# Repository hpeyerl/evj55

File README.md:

# Before

# Maybe

Files related to my EV conversion project.

## Related repos

- [evj55-dashboard](https://github.com/hpeyerl/evj55-dashboard) - dashboard firmware (Radxa CM3 + dual-CAN HAT+)
- [Wiring Harness](wiring/splice-cad-rendered/EVJ-55_plan_all_pages_schematic.pdf)

# Network system diagram

# Mechanical/Electrical system diagram

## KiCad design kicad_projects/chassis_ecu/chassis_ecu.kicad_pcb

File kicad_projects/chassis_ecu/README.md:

# chassis_ecu

ESP32-S3 CAN board for the parking pawl, J1772 pilot and contactor-weld sense.
The EPB stays on the Revus controller. Spec: `evj55_contexts/CHASSIS_ECU_CONTEXT.md`.

The schematic is generated. Edit `gen/chassis_ecu.py`, then:

    cd gen && /usr/bin/python3 build.py

`build.py` rewrites the `*.kicad_sch` files, runs `kicad-cli` ERC, and checks the exported
netlist against the definition (every pin on its intended net). Use the system python: KiCad's
libraries and `pcbnew` are installed there.

Parts are hand-placed in the generator and wired; the generator is the master copy (do not save
schematic edits made in KiCad).

## Requirements
What the schematic must satisfy. Review against these.

**Jobs:** parking-pawl drive, J1772 car-side pilot (CP) and proximity (PP), contactor-weld sense,
brake / P-position inputs, 2 analog inputs, 6-axis IMU, one CAN bus. The EPB is NOT on this board.

**Supply (J20 A2, switched 12V):**
- Steady state <= 15 V (DC-DC fed, no alternator). Spikes from inductive kickback, wiring ring and
  terminal let-go (microseconds) must be clamped; no sustained overvoltage.
- Reverse battery must not damage the logic side and must not blow the board fuse.
- Starts at about 6 V (UVLO). 3.3 V rail >= 1 A (ESP32 + CAN + sensors, ~0.6 A peak estimate).
- Low sleep current is wanted (an optional harness change feeds the board from permanent B+).

**Opto inputs x4 (J20 B2-B5: P_SENSE, BRAKE, WELD1, WELD2):** 12V-active, opto-coupled (level shift
and robustness; NOT isolated - the inputs share vehicle GND), active-low at the GPIO, filtered.
WELD1/WELD2 are the contactors' dry aux contacts (open = no voltage). P_SENSE taps a sense line shared with other loads, so it must draw little current.

**Pawl output (J20 A1/B1 feed, A8/B8 out):** high-side 12 V switch to the actuator (the actuator's
other lead grounds at the motor). Current sense for stall detection; firmware enforces a run
timeout. Design stall current 20 A (actual stall current not yet measured). No reverse protection on
the motor feed: the external harness fuse protects it.

**J1772 (J20 C2 CP, C3 CP_GND, C4 PP), car side - the board never generates the pilot:**
- CP -> diode -> 2.74 k to GND (state B); + 1.3 k switched in parallel (state C).
- The state-C switch must be CLOSED when the board is unpowered (12V box dead before AC arrives,
  so a dead board must still request charge). Firmware opens it to hold state B (pause / stop).
- Read CP duty (1 kHz, 10-96 %) and CP high level (+12 / +9 / +6 V = state A / B / C).
- Survive the +/-12 V CP swing; load on CP >= 100 k.
- Read PP: open / plug inserted / latch button pressed must be distinguishable.

**CAN:** one classic CAN bus (truck CAN1), in and out pins on J20 for daisy-chaining. No glitch
on CAN TX at power-up. Transceiver standby under firmware control (sleep current). 120R
terminator selectable, default off (mid-bus). Bus TVS. Firmware emulates the Zombie CPC (TX 0x357,
RX 0x358).

**Analog inputs AIN1/AIN2 (J20 B6/B7):** 0-15 V into the ESP32 ADC1 (effective range 0-2.9 V), survive reverse / overvoltage
spikes. Coarse accuracy is fine. 12 V logic supply sensed on ADC1 as well.

**IMU:** 6-axis accel + gyro on I2C, no magnetometer. The board mounts square to the vehicle axes.

**MCU / debug:** ESP32-S3 module with PCB antenna (plastic case). USB for programming (data only;
the board runs from 12 V). UART header (DNP) as a fallback console. BOOT / RESET as jumper pads.
Expansion header J10 (DNP): I2C, 3 raw ADC1, 2 GPIO.

**Mechanical / manufacture:**
- PCB 82 x 101 mm in the case; J20 centred on an 82 mm edge.
- Case height 33 mm only over the third nearest J20: tall parts go there.
- JLC assembly with LCSC parts; J20 and test points are hand-soldered.
- A labelled GND test point for scope / logic-analyser clips.
- Automotive: conformal coat.

## PCB
`chassis_ecu.kicad_pcb` was created once by `gen/make_pcb.py`: 82 x 101 mm outline (3 mm corners,
J20 key notch), 4 layers, J20 centred on the top edge, ESP32 antenna flush with the bottom edge
(copper keep-out under it), case holes, first-pass block placement (tall parts in the top third).
The script refuses to overwrite an existing board (`--force` discards it). From here: edit in KiCad,
"Update PCB from Schematic" after schematic changes. Expected DRC items: U2 courtyard (on-board
antenna keep-out, not used here) and the paired case holes H1/H2, H3/H4 overlap.

## Parts / BOM
- `gen/jlc_select.py <cache.sqlite3>` picks LCSC parts from the jlcparts database
  (yaqwsx.github.io/jlcparts/data/cache.zip + cache.z01..z05, a split zip of one 2.1 GB sqlite file;
  the concatenated parts start with a 4-byte split marker) and writes `gen/lcsc_parts.json`.
  Preference: in stock, JLC basic > preferred > extended.
- `gen/bom.py` writes `chassis_ecu_bom_jlc.csv` (JLCPCB assembly format).
- U2 = ESP32-S3-WROOM-1-N4 (LCSC C2913197), JLC-assembled; 4 MB = 2 x ~1.9 MB OTA slots (min_spiffs).
  Not assembled by JLC: connectors (J20 = through-hole), BOOT/RESET jumper pads,
  solder jumpers, test points.
- 55 BOM lines, 117 placements. Low JLC stock (< 5000) on the
  BTN8982TA, CPC1117N, FDD4685, LSM6DSOX, SMCJ22A, TLV3201 - recheck at order time.

## Status
- Drawn (0 ERC errors, netlist self-check OK): Power, MCU, CAN (1 bus, native TWAI), IO (4 opto
  inputs, status LEDs, J10 expansion), Motors (pawl high-side, BTN8982TA), J1772 (CP state + read,
  PP read), Sensors (LSM6DSO, 2x 12V-tolerant AIN), Connector.
- Main connector J20 = Aptiv/FCI HCCPHPE24BKA90F (24-way 90 deg, key A), mates 211PC249S0005.
  Footprint from FCI drawing FSC 308654: `lib/` (generated by `gen/make_lib.py`). Footprint
  confirmed with a 1:1 printout against a real header.
- Case (listing drawing, to verify on the real part): PCB 82 x 101 mm; J20 centred on an 82 mm edge;
  4x 2.5 mm mounting holes = 2 slotted pairs (6 mm apart) at 62.2 mm centres, lower holes 7.4 mm from
  the edge opposite J20. Case outside 120 x 121 x 33 mm.
- 3D model: vendor STEP is not redistributable; put `HCCPHPE24BKA90F.stp` in `lib/3d/` (git-ignored).
- 4 ERC warnings: the SparkFun LSM6DSOX symbol types its strap pins bidirectional (benign).
- Design stall current 20 A.  PP is read on this board
  (Zombie `interface=CPC`).  Open: routing.

## ESP32-S3 pin map
| GPIO | Net | GPIO | Net |
|---|---|---|---|
| IO0 | ESP_BOOT (JP4 pad) | IO35-38 | OPTO_IN1-4 (P_SENSE, BRAKE, WELD1, WELD2; active-low) |
| IO1 | CP_LVL (ADC1) | IO39 | PAWL_INH (10k pull-down) |
| IO2 | PP_SENSE (ADC1) | IO40 | CAN1_TXD |
| IO4 / IO5 / IO10 | ANA1-3 (ADC1, J10) | IO21 | CAN1_RXD |
| IO6 | PAWL_IS (ADC1) | IO41 | CP_DUTY |
| IO7 | VSENSE_12V (ADC1) | IO42 | CP_S2_OPEN |
| IO8 / IO9 | AIN1 / AIN2 (ADC1, J20) | IO47 | IMU_INT1 |
| IO11 / IO12 | EXP_GPIO1 / 2 (J10) | IO48 | PAWL_DRV |
| IO15 / IO16 | I2C_SDA / I2C_SCL | IO17 / IO18 | LED_STAT1 / LED_STAT2 |
| IO13 | CAN1_RS (low = run, high = standby; 10k pull-down) | | |
| IO19 / IO20 | USB D- / D+ | IO43 / IO44 | UART TX / RX (J2, DNP) |
| unused | IO14 | strapping, NC | IO3, IO45, IO46 |

## I2C
0x6A LSM6DSO. J10 brings the bus out for add-ons.

## J10 expansion (DNP)
1 GND, 2 3V3, 3 SDA, 4 SCL, 5-7 ANA1-3 (raw ADC1, 0-2.9 V), 8-9 EXP_GPIO1/2, 10 GND.

## J20 pinout (columns 1 and 8 = high-current cavities)
| Pin | Net | Pin | Net | Pin | Net |
|---|---|---|---|---|---|
| A1 | PAWL_12V | B1 | PAWL_12V | C1 | GND |
| A2 | VIN_12V | B2 | IN_P_SENSE | C2 | CP |
| A3 | CAN1_H in | B3 | IN_BRAKE | C3 | CP_GND |
| A4 | CAN1_L in | B4 | IN_WELD1 | C4 | PP |
| A5 | CAN1_H out | B5 | IN_WELD2 | C5 | spare |
| A6 | CAN1_L out | B6 | AIN1 (0-15 V) | C6 | spare |
| A7 | GND | B7 | AIN2 (0-15 V) | C7 | spare |
| A8 | MOT_OUT | B8 | MOT_OUT | C8 | GND |

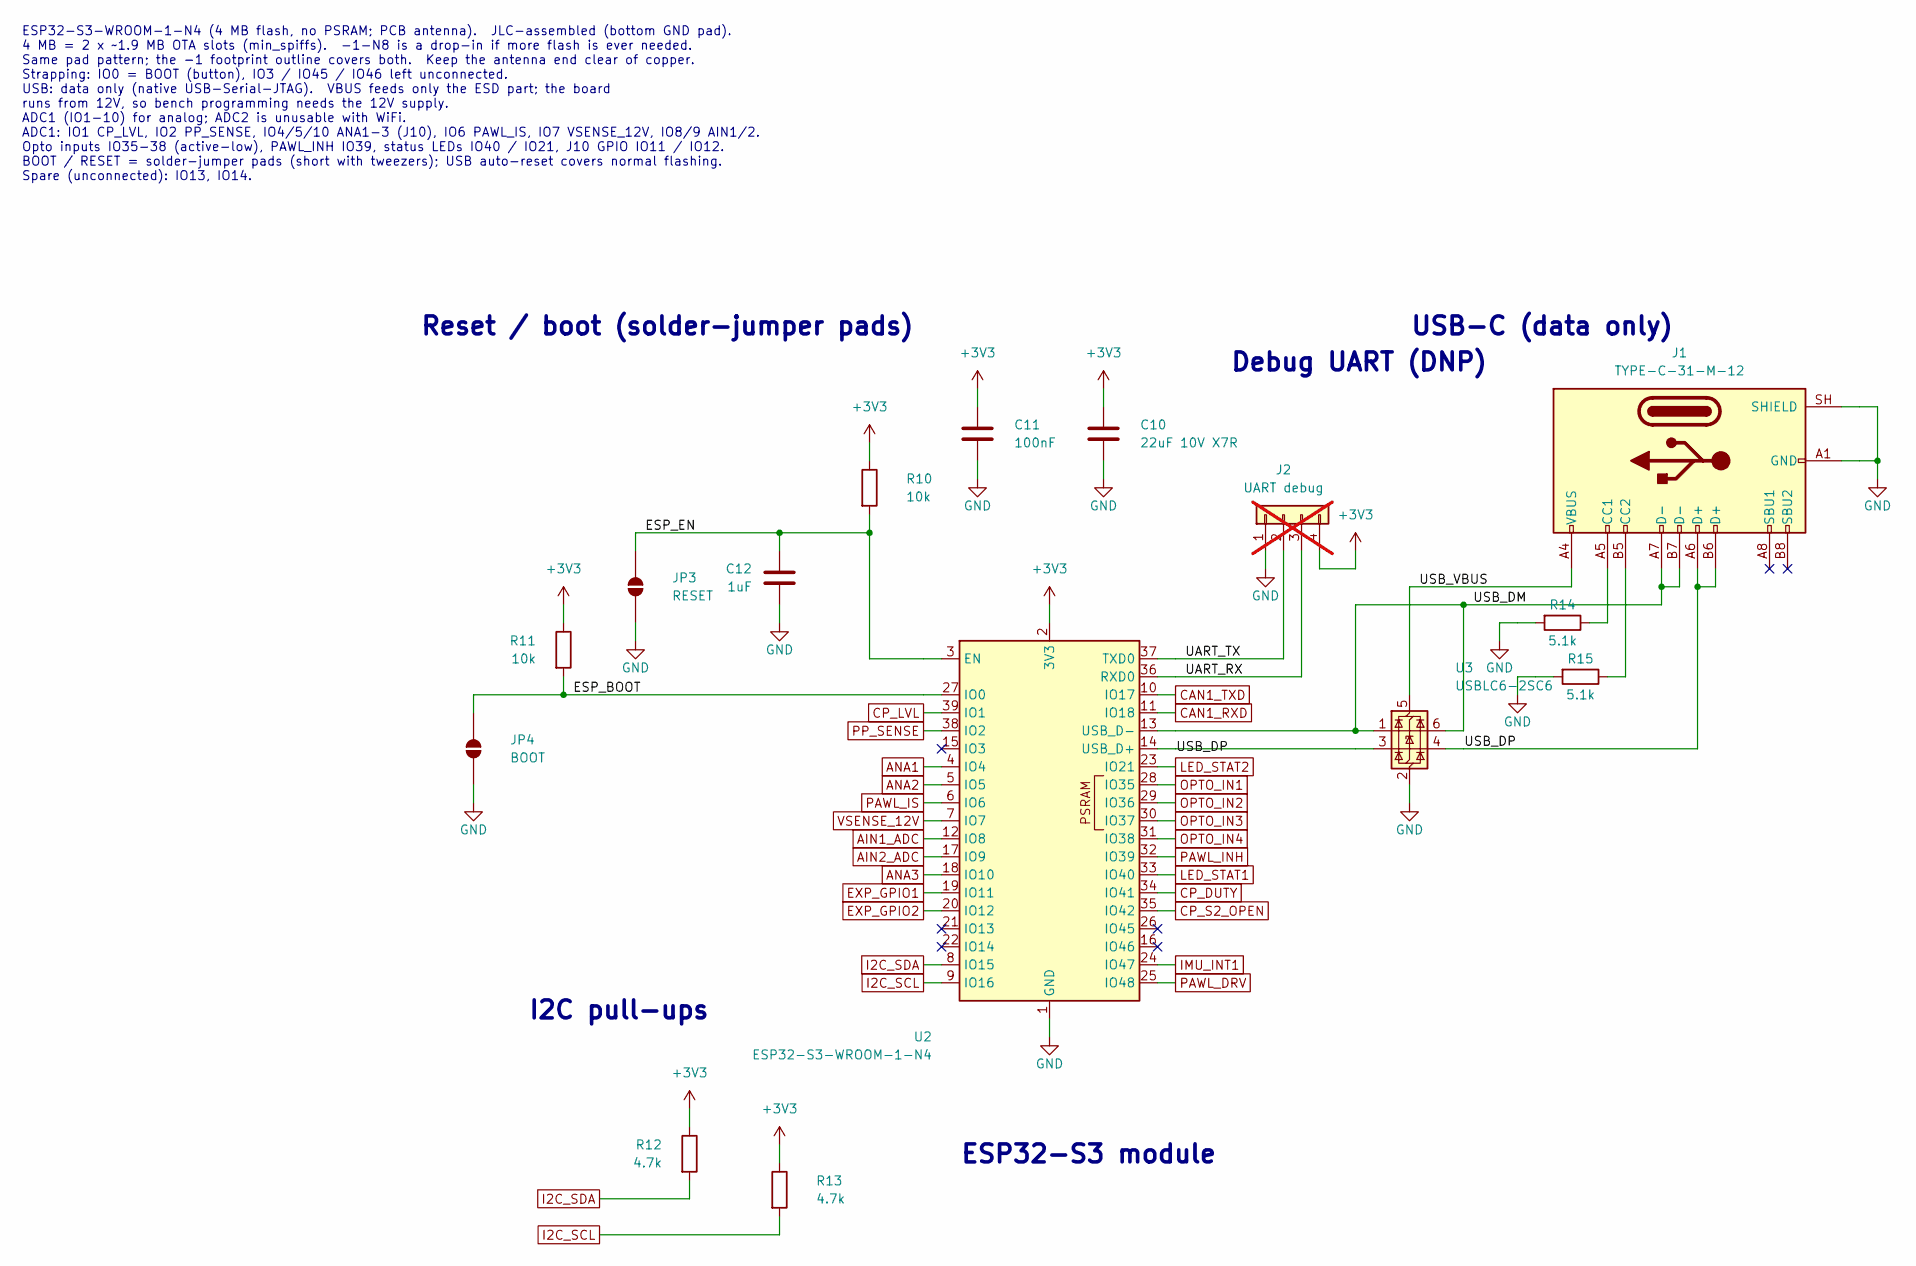
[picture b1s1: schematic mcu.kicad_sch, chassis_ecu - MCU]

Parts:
C10: 22uF 10V X7R; C_1206_3216Metric; MPN CL31A226KAHNNNE; LCSC C12891
C11: 100nF; C_0603_1608Metric; MPN CC0603KRX7R9BB104; LCSC C14663
C12: 1uF; C_0603_1608Metric; MPN CL10A105KB8NNNC; LCSC C15849
J1: TYPE-C-31-M-12; USB_C_Receptacle_HRO_TYPE-C-31-M-12; MPN TYPE-C-31-M-12; LCSC C165948
J2: UART debug; PinHeader_1x04_P2.54mm_Vertical; not fitted
JP3: RESET; SolderJumper-2_P1.3mm_Open_RoundedPad1.0x1.5mm; MPN TS-1187A-B-A-B; LCSC C318884
JP4: BOOT; SolderJumper-2_P1.3mm_Open_RoundedPad1.0x1.5mm; MPN TS-1187A-B-A-B; LCSC C318884
R10, R11: 10k; R_0603_1608Metric; MPN 0603WAF1002T5E; LCSC C25804
R12, R13: 4.7k; R_0603_1608Metric; MPN 0603WAF4701T5E; LCSC C23162
R14, R15: 5.1k; R_0603_1608Metric; MPN 0603WAF5101T5E; LCSC C23186
U2: ESP32-S3-WROOM-1-N4; ESP32-S3-WROOM-1; LCSC C2913197
U3: USBLC6-2SC6; SOT-23-6; MPN USBLC6-2SC6; LCSC C7519

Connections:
+3V3: C10.1, C11.1, J2.4, R10.1, R11.1, R12.1, R13.1, U2.2 (3V3); also elsewhere on the board
/MCU/ESP_BOOT: JP4.1 (A), R11.2, U2.27 (IO0)
/MCU/ESP_EN: C12.1, JP3.1 (A), R10.2, U2.3 (EN)
/MCU/UART_RX: J2.3, U2.36 (RXD0)
/MCU/UART_TX: J2.2, U2.37 (TXD0)
/MCU/USB_CC1: J1.A5 (CC1), R14.1
/MCU/USB_CC2: J1.B5 (CC2), R15.1
/MCU/USB_DM: J1.A7 (D-), J1.B7 (D-), U2.13 (USB_D-), U3.1 (I/O1), U3.6 (I/O1)
/MCU/USB_DP: J1.A6 (D+), J1.B6 (D+), U2.14 (USB_D+), U3.3 (I/O2), U3.4 (I/O2)
/MCU/USB_VBUS: J1.A4 (VBUS), J1.A9 (VBUS), J1.B4 (VBUS), J1.B9 (VBUS), U3.5 (VBUS)
AIN1_ADC: U2.12 (IO8); also elsewhere on the board
AIN2_ADC: U2.17 (IO9); also elsewhere on the board
ANA1: U2.4 (IO4); also elsewhere on the board
ANA2: U2.5 (IO5); also elsewhere on the board
ANA3: U2.18 (IO10); also elsewhere on the board
CAN1_RXD: U2.11 (IO18); also elsewhere on the board
CAN1_TXD: U2.10 (IO17); also elsewhere on the board
CP_DUTY: U2.34 (IO41); also elsewhere on the board
CP_LVL: U2.39 (IO1); also elsewhere on the board
CP_S2_OPEN: U2.35 (IO42); also elsewhere on the board
EXP_GPIO1: U2.19 (IO11); also elsewhere on the board
EXP_GPIO2: U2.20 (IO12); also elsewhere on the board
GND: C10.2, C11.2, C12.2, J1.A1 (GND), J1.A12 (GND), J1.B1 (GND), J1.B12 (GND), J1.SH (SHIELD), J2.1, JP3.2 (B), JP4.2 (B), R14.2, R15.2, U2.1 (GND), U2.40 (GND), U2.41 (GND), U3.2 (GND); also elsewhere on the board
I2C_SCL: R13.2, U2.9 (IO16); also elsewhere on the board
I2C_SDA: R12.2, U2.8 (IO15); also elsewhere on the board
IMU_INT1: U2.24 (IO47); also elsewhere on the board
LED_STAT1: U2.33 (IO40); also elsewhere on the board
LED_STAT2: U2.23 (IO21); also elsewhere on the board
OPTO_IN1: U2.28 (IO35); also elsewhere on the board
OPTO_IN2: U2.29 (IO36); also elsewhere on the board
OPTO_IN3: U2.30 (IO37); also elsewhere on the board
OPTO_IN4: U2.31 (IO38); also elsewhere on the board
PAWL_DRV: U2.25 (IO48); also elsewhere on the board
PAWL_INH: U2.32 (IO39); also elsewhere on the board
PAWL_IS: U2.6 (IO6); also elsewhere on the board
PP_SENSE: U2.38 (IO2); also elsewhere on the board
VSENSE_12V: U2.7 (IO7); also elsewhere on the board

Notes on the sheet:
I2C pull-ups
Debug UART (DNP)
ESP32-S3-WROOM-1-N4 (4 MB flash, no PSRAM; PCB antenna). JLC-assembled (bottom GND pad). 4 MB = 2 x ~1.9 MB OTA slots (min_spiffs). -1-N8 is a drop-in if more flash is ever needed. Same pad pattern; the -1 footprint outline covers both. Keep the antenna end clear of copper. Strapping: IO0 = BOOT (b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
Reset / boot (solder-jumper pads)
ESP32-S3 module
USB-C (data only)

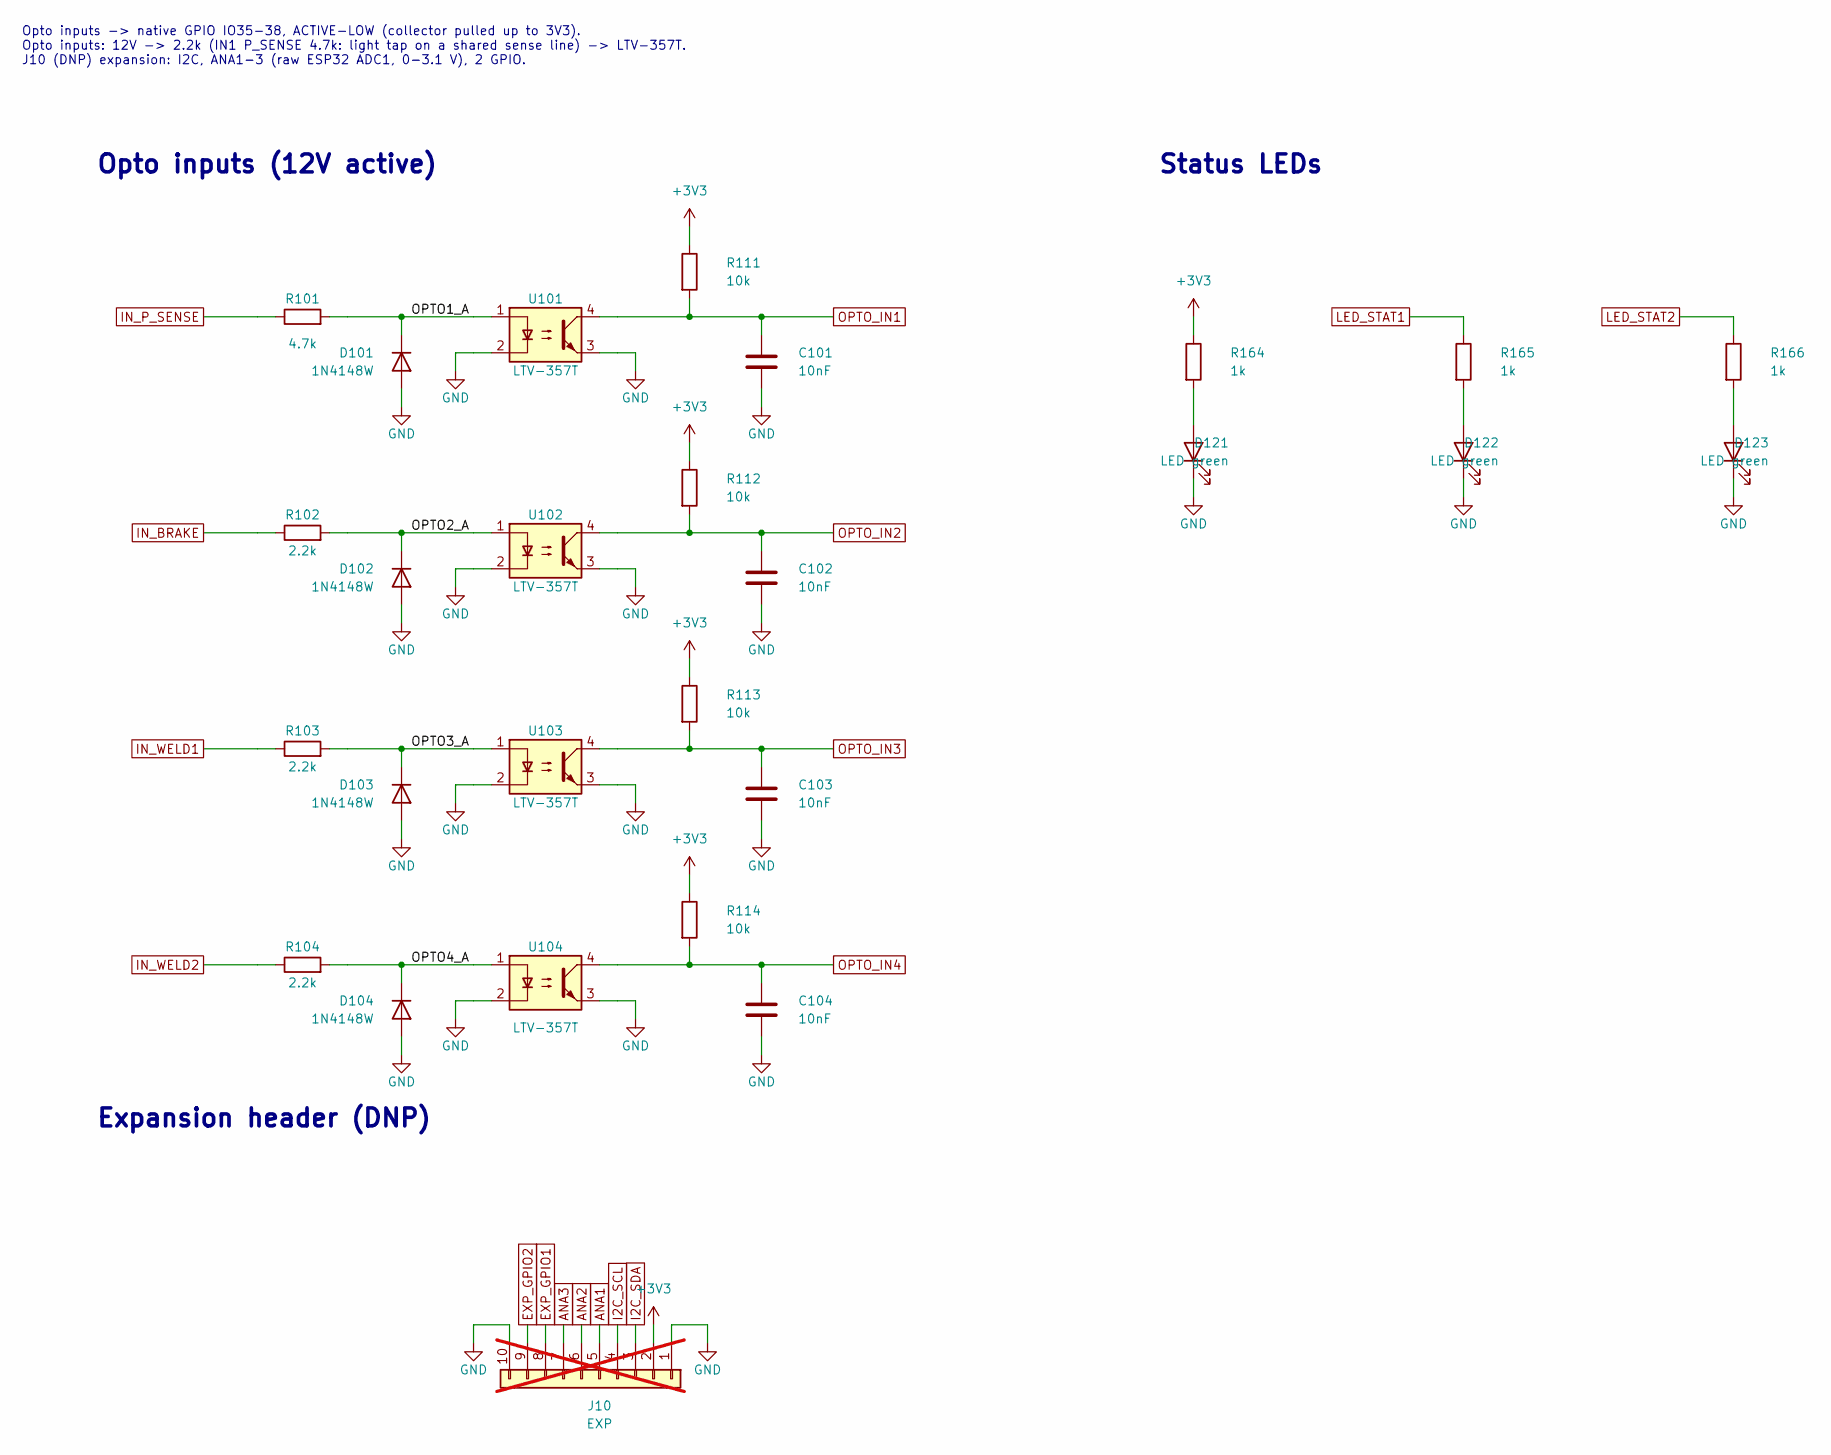
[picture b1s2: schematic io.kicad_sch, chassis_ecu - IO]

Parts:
C101, C102, C103, C104: 10nF; C_0603_1608Metric; MPN 0603B103K500NT; LCSC C57112
D101, D102, D103, D104: 1N4148W; D_SOD-123; MPN 1N4148W; LCSC C81598
D121, D122, D123: LED green; LED_0603_1608Metric; MPN F.0603.00025/P2-0603G1TS2-06T-002; LCSC C7496818
J10: EXP; PinHeader_1x10_P2.54mm_Vertical; not fitted
R101: 4.7k; R_0805_2012Metric; MPN 0805W8F4701T5E; LCSC C17673
R102, R103, R104: 2.2k; R_0805_2012Metric; MPN 0805W8F2201T5E; LCSC C17520
R111, R112, R113, R114: 10k; R_0603_1608Metric; MPN 0603WAF1002T5E; LCSC C25804
R164, R165, R166: 1k; R_0603_1608Metric; MPN 0603WAF1001T5E; LCSC C21190
U101, U102, U103, U104: LTV-357T; SO-4_4.4x3.6mm_P2.54mm; MPN LTV-357T-C; LCSC C119091

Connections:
+3V3: J10.2, R111.1, R112.1, R113.1, R114.1, R164.1; also elsewhere on the board
/IO/LED1_A: D122.2 (A), R165.2
/IO/LED2_A: D123.2 (A), R166.2
/IO/LED_PWR_A: D121.2 (A), R164.2
/IO/OPTO1_A: D101.1 (K), R101.2, U101.1
/IO/OPTO2_A: D102.1 (K), R102.2, U102.1
/IO/OPTO3_A: D103.1 (K), R103.2, U103.1
/IO/OPTO4_A: D104.1 (K), R104.2, U104.1
ANA1: J10.5; also elsewhere on the board
ANA2: J10.6; also elsewhere on the board
ANA3: J10.7; also elsewhere on the board
EXP_GPIO1: J10.8; also elsewhere on the board
EXP_GPIO2: J10.9; also elsewhere on the board
GND: C101.2, C102.2, C103.2, C104.2, D101.2 (A), D102.2 (A), D103.2 (A), D104.2 (A), D121.1 (K), D122.1 (K), D123.1 (K), J10.1, J10.10, U101.2, U101.3, U102.2, U102.3, U103.2, U103.3, U104.2, U104.3; also elsewhere on the board
I2C_SCL: J10.4; also elsewhere on the board
I2C_SDA: J10.3; also elsewhere on the board
IN_BRAKE: R102.1; also elsewhere on the board
IN_P_SENSE: R101.1; also elsewhere on the board
IN_WELD1: R103.1; also elsewhere on the board
IN_WELD2: R104.1; also elsewhere on the board
LED_STAT1: R165.1; also elsewhere on the board
LED_STAT2: R166.1; also elsewhere on the board
OPTO_IN1: C101.1, R111.2, U101.4; also elsewhere on the board
OPTO_IN2: C102.1, R112.2, U102.4; also elsewhere on the board
OPTO_IN3: C103.1, R113.2, U103.4; also elsewhere on the board
OPTO_IN4: C104.1, R114.2, U104.4; also elsewhere on the board

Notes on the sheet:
Opto inputs (12V active)
Opto inputs -> native GPIO IO35-38, ACTIVE-LOW (collector pulled up to 3V3). Opto inputs: 12V -> 2.2k (IN1 P_SENSE 4.7k: light tap on a shared sense line) -> LTV-357T. J10 (DNP) expansion: I2C, ANA1-3 (raw ESP32 ADC1, 0-3.1 V), 2 GPIO.
Status LEDs
Expansion header (DNP)

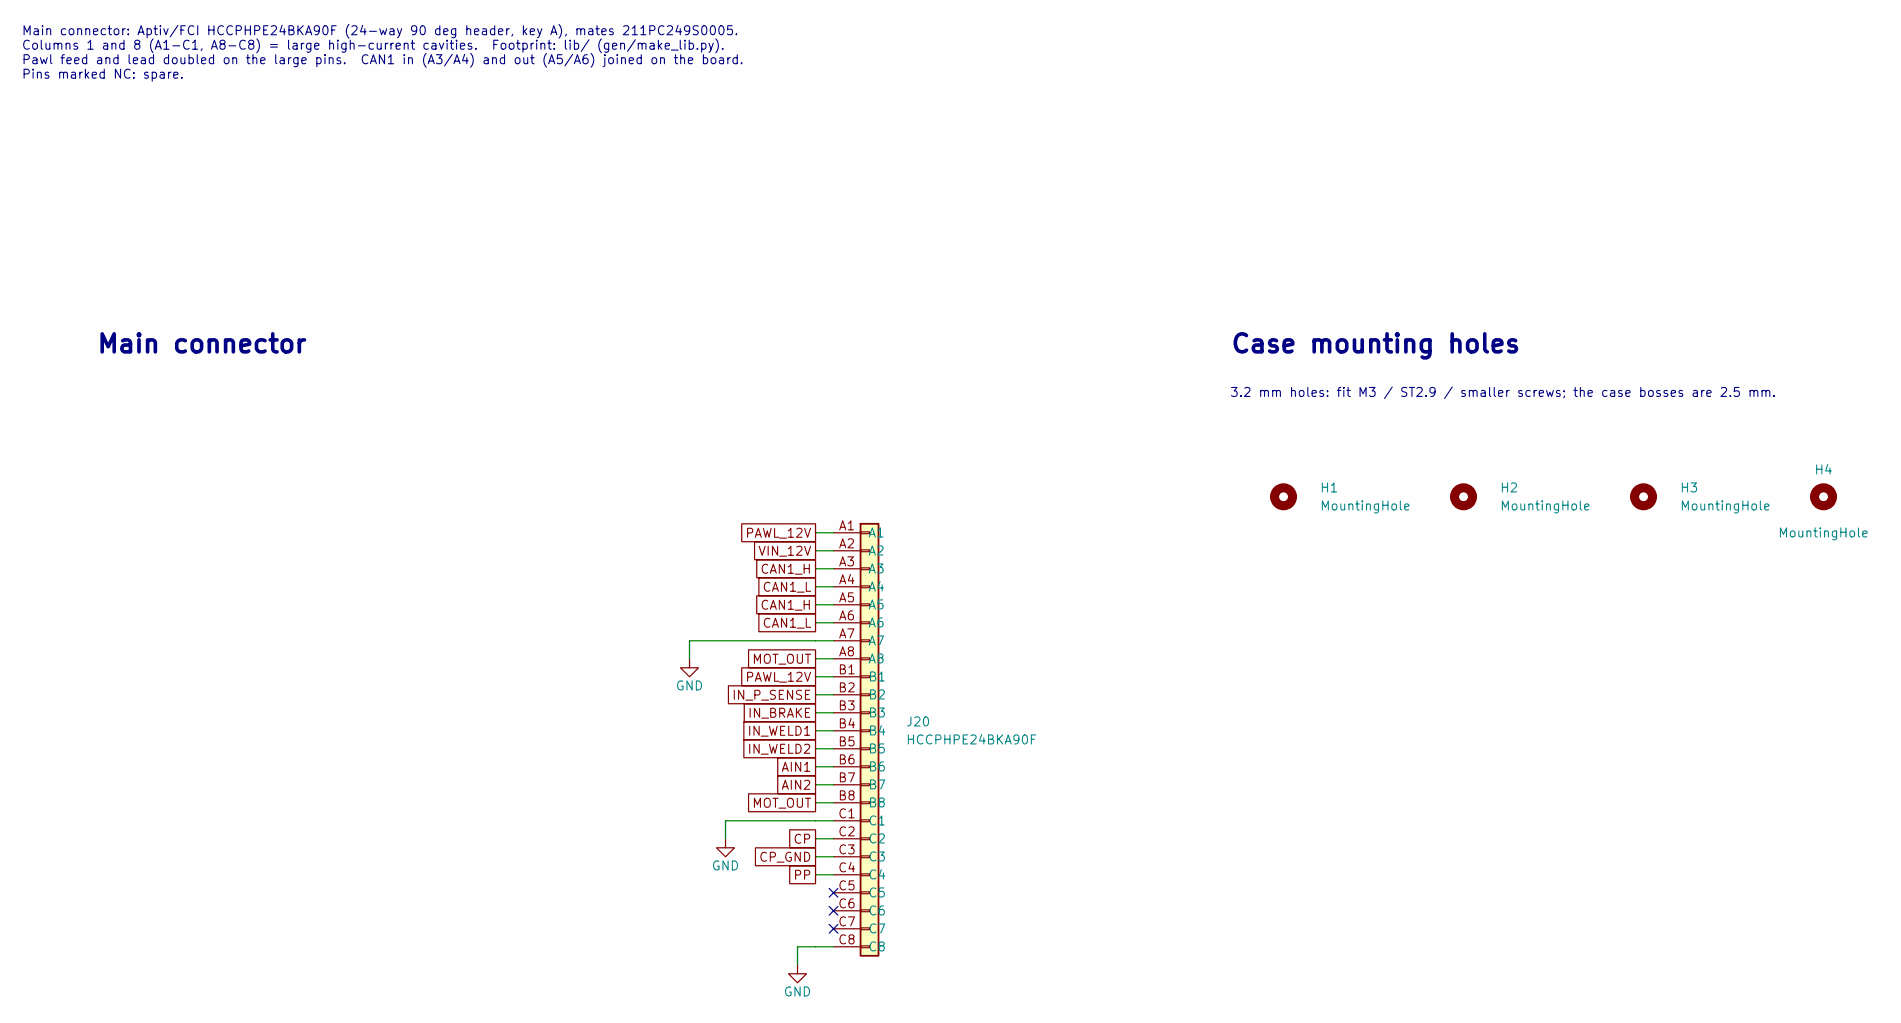
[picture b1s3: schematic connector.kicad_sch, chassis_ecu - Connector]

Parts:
H1, H2, H3, H4: MountingHole; MountingHole_3.2mm_M3; JLC not a part
J20: HCCPHPE24BKA90F; FCI_HCCPHPE24BKA90F; JLC not assembled - hand-solder (through-ho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

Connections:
AIN1: J20.B6; also elsewhere on the board
AIN2: J20.B7; also elsewhere on the board
CAN1_H: J20.A3, J20.A5; also elsewhere on the board
CAN1_L: J20.A4, J20.A6; also elsewhere on the board
CP: J20.C2; also elsewhere on the board
CP_GND: J20.C3; also elsewhere on the board
GND: J20.A7, J20.C1, J20.C8; also elsewhere on the board
IN_BRAKE: J20.B3; also elsewhere on the board
IN_P_SENSE: J20.B2; also elsewhere on the board
IN_WELD1: J20.B4; also elsewhere on the board
IN_WELD2: J20.B5; also elsewhere on the board
MOT_OUT: J20.A8, J20.B8; also elsewhere on the board
PAWL_12V: J20.A1, J20.B1; also elsewhere on the board
PP: J20.C4; also elsewhere on the board
VIN_12V: J20.A2; also elsewhere on the board

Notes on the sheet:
3.2 mm holes: fit M3 / ST2.9 / smaller screws; the case bosses are 2.5 mm.
Main connector: Aptiv/FCI HCCPHPE24BKA90F (24-way 90 deg header, key A), mates 211PC249S0005. Columns 1 and 8 (A1-C1, A8-C8) = large high-current cavities. Footprint: lib/ (gen/make_lib.py). Pawl feed and lead doubled on the large pins. CAN1 in (A3/A4) and out (A5/A6) joined on the board. Pins mark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
Case mounting holes
Main connector

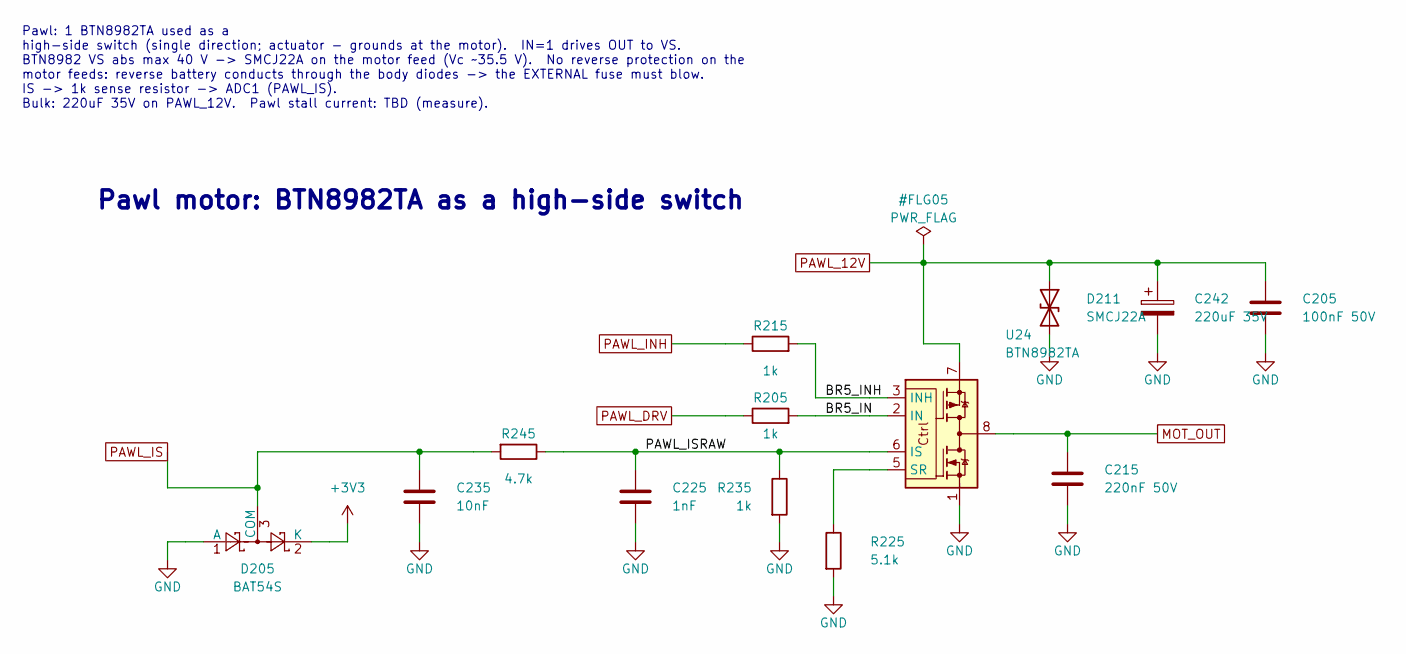
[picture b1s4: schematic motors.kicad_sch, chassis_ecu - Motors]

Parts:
C205: 100nF 50V; C_0603_1608Metric; MPN CC0603KRX7R9BB104; LCSC C14663
C215: 220nF 50V; C_0805_2012Metric; MPN CL21B224KBFNNNE; LCSC C5378
C225: 1nF; C_0603_1608Metric; MPN CL10B102KB8NNNC; LCSC C1588
C235: 10nF; C_0603_1608Metric; MPN 0603B103K500NT; LCSC C57112
C242: 220uF 35V; CP_Elec_8x10.5; MPN UCD1V221MNL1GS; LCSC C136294
D205: BAT54S; SOT-23; MPN BAT54S; LCSC C7420333
D211: SMCJ22A; D_SMC; MPN SMCJ22A; LCSC C383717
R205, R215, R235: 1k; R_0603_1608Metric; MPN 0603WAF1001T5E; LCSC C21190
R225: 5.1k; R_0603_1608Metric; MPN 0603WAF5101T5E; LCSC C23186
R245: 4.7k; R_0603_1608Metric; MPN 0603WAF4701T5E; LCSC C23162
U24: BTN8982TA; TO-263-7_TabPin8; MPN BTN8982TA; LCSC C74175

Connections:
+3V3: D205.2 (K); also elsewhere on the board
/Motors/BR5_IN: R205.2, U24.2 (IN)
/Motors/BR5_INH: R215.2, U24.3 (INH)
/Motors/BR5_SR: R225.1, U24.5 (SR)
/Motors/PAWL_ISRAW: C225.1, R235.1, R245.1, U24.6 (IS)
GND: C205.2, C215.2, C225.2, C235.2, C242.2, D205.1 (A), D211.2 (A2), R225.2, R235.2, U24.1; also elsewhere on the board
MOT_OUT: C215.1, U24.4, U24.8; also elsewhere on the board
PAWL_12V: C205.1, C242.1, D211.1 (A1), U24.7; also elsewhere on the board
PAWL_DRV: R205.1; also elsewhere on the board
PAWL_INH: R215.1; also elsewhere on the board
PAWL_IS: C235.1, D205.3 (COM), R245.2; also elsewhere on the board

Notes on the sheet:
Pawl: 1 BTN8982TA used as a high-side switch (single direction; actuator - grounds at the motor). IN=1 drives OUT to VS. BTN8982 VS abs max 40 V -> SMCJ22A on the motor feed (Vc ~35.5 V). No reverse protection on the motor feeds: reverse battery conducts through the body diodes -> the EXTERNAL fuse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
Pawl motor: BTN8982TA as a high-side switch

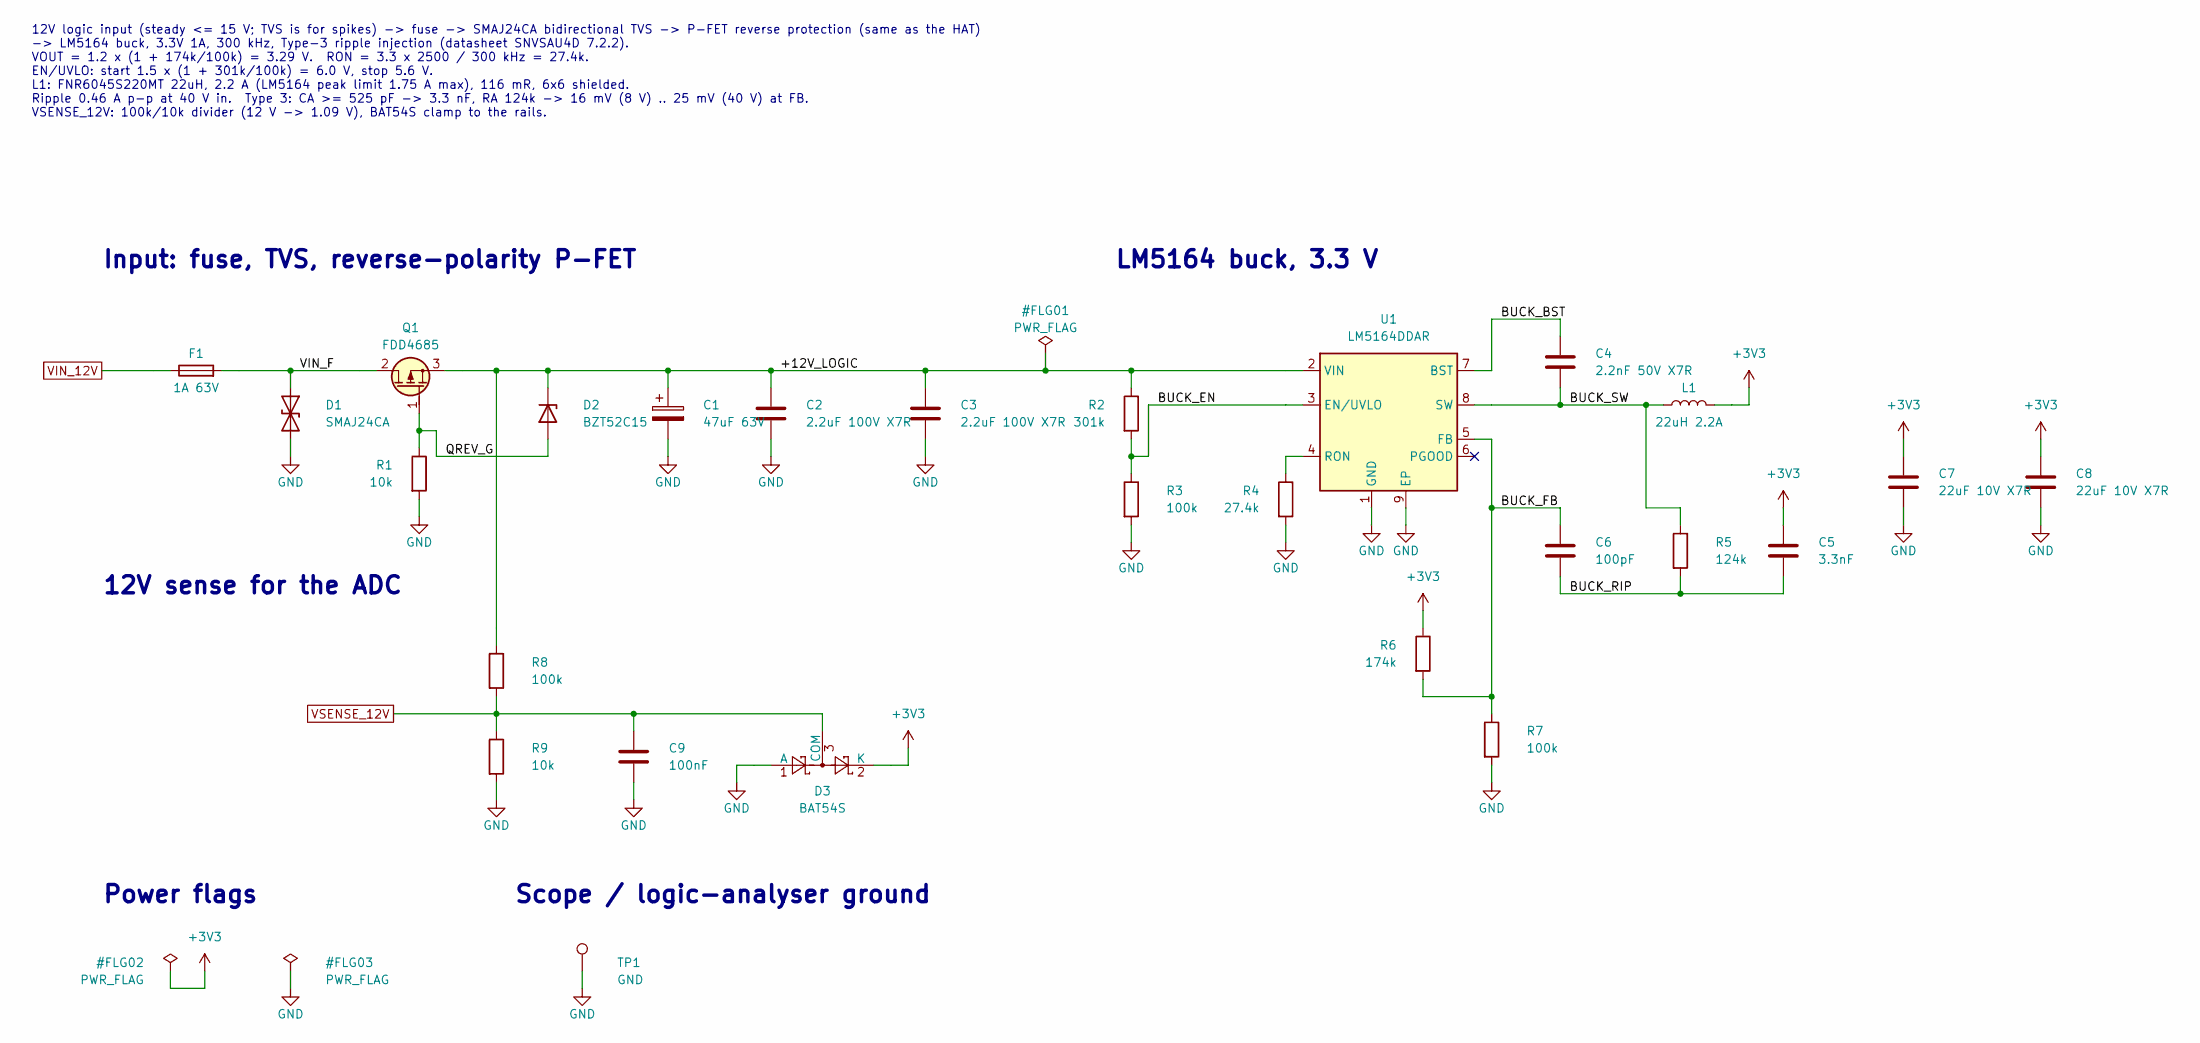
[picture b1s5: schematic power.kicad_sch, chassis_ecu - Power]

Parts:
C1: 47uF 63V; CP_Elec_6.3x7.7; MPN RV63V47M6X8; LCSC C48971005
C2, C3: 2.2uF 100V X7R; C_1210_3225Metric; MPN FS32X225K101EGG; LCSC C153036
C4: 2.2nF 50V X7R; C_0603_1608Metric; MPN 0603B222K500NT; LCSC C1604
C5: 3.3nF; C_0603_1608Metric; MPN CL10B332KB8NNNC; LCSC C1613
C6: 100pF; C_0603_1608Metric; MPN CL10C101JB8NNNC; LCSC C14858
C7, C8: 22uF 10V X7R; C_1206_3216Metric; MPN CL31A226KAHNNNE; LCSC C12891
C9: 100nF; C_0603_1608Metric; MPN CC0603KRX7R9BB104; LCSC C14663
D1: SMAJ24CA; D_SMA; MPN SMAJ24CA; LCSC C19077542
D2: BZT52C15; D_SOD-123; MPN BZT52C15; LCSC C19077412
D3: BAT54S; SOT-23; MPN BAT54S; LCSC C7420333
F1: 1A 63V; Fuse_1206_3216Metric; MPN 0466001.NRHF; LCSC C151135
L1: 22uH 2.2A; L_Changjiang_FNR6045S; MPN FNR6045S220MT; LCSC C168080
Q1: FDD4685; TO-252-2; MPN FDD4685; LCSC C258227
R1, R9: 10k; R_0603_1608Metric; MPN 0603WAF1002T5E; LCSC C25804
R2: 301k; R_0603_1608Metric; MPN 0603WAF3013T5E; LCSC C23026
R3, R7, R8: 100k; R_0603_1608Metric; MPN 0603WAF1003T5E; LCSC C25803
R4: 27.4k; R_0603_1608Metric; MPN CRCW060327K4FKEA; LCSC C843937
R5: 124k; R_0603_1608Metric; MPN 0603WAF1243T5E; LCSC C22788
R6: 174k; R_0603_1608Metric; MPN 0603WAF1743T5E; LCSC C22890
TP1: GND; TestPoint_Keystone_5000-5004_Miniature; MPN Keystone 5001 (black); JLC not assembled - hand-solder (through-ho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
U1: LM5164DDAR; HSOP-8-1EP_3.9x4.9mm_P1.27mm_EP2.41x3.1mm_ThermalVias; MPN LM5164DDAR; LCSC C477928

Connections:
+3V3: C5.2, C7.1, C8.1, D3.2 (K), L1.2, R6.1; also elsewhere on the board
/Power/+12V_LOGIC: C1.1, C2.1, C3.1, D2.1 (K), Q1.3 (S), R2.1, R8.1, U1.2 (VIN)
/Power/BUCK_BST: C4.1, U1.7 (BST)
/Power/BUCK_EN: R2.2, R3.1, U1.3 (EN/UVLO)
/Power/BUCK_FB: C6.2, R6.2, R7.1, U1.5 (FB)
/Power/BUCK_RIP: C5.1, C6.1, R5.2
/Power/BUCK_RON: R4.1, U1.4 (RON)
/Power/BUCK_SW: C4.2, L1.1, R5.1, U1.8 (SW)
/Power/QREV_G: D2.2 (A), Q1.1 (G), R1.1
/Power/VIN_F: D1.1 (A1), F1.2, Q1.2 (D)
GND: C1.2, C2.2, C3.2, C7.2, C8.2, C9.2, D1.2 (A2), D3.1 (A), R1.2, R3.2, R4.2, R7.2, R9.2, TP1.1, U1.1 (GND), U1.9 (EP); also elsewhere on the board
VIN_12V: F1.1; also elsewhere on the board
VSENSE_12V: C9.1, D3.3 (COM), R8.2, R9.1; also elsewhere on the board

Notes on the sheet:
12V sense for the ADC
Power flags
Scope / logic-analyser ground
Input: fuse, TVS, reverse-polarity P-FET
LM5164 buck, 3.3 V
12V logic input (steady <= 15 V; TVS is for spikes) -> fuse -> SMAJ24CA bidirectional TVS -> P-FET reverse protection (same as the HAT) -> LM5164 buck, 3.3V 1A, 300 kHz, Type-3 ripple injection (datasheet SNVSAU4D 7.2.2). VOUT = 1.2 x (1 + 174k/100k) = 3.29 V. RON = 3.3 x 2500 / 300 kHz = 27.4k. EN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

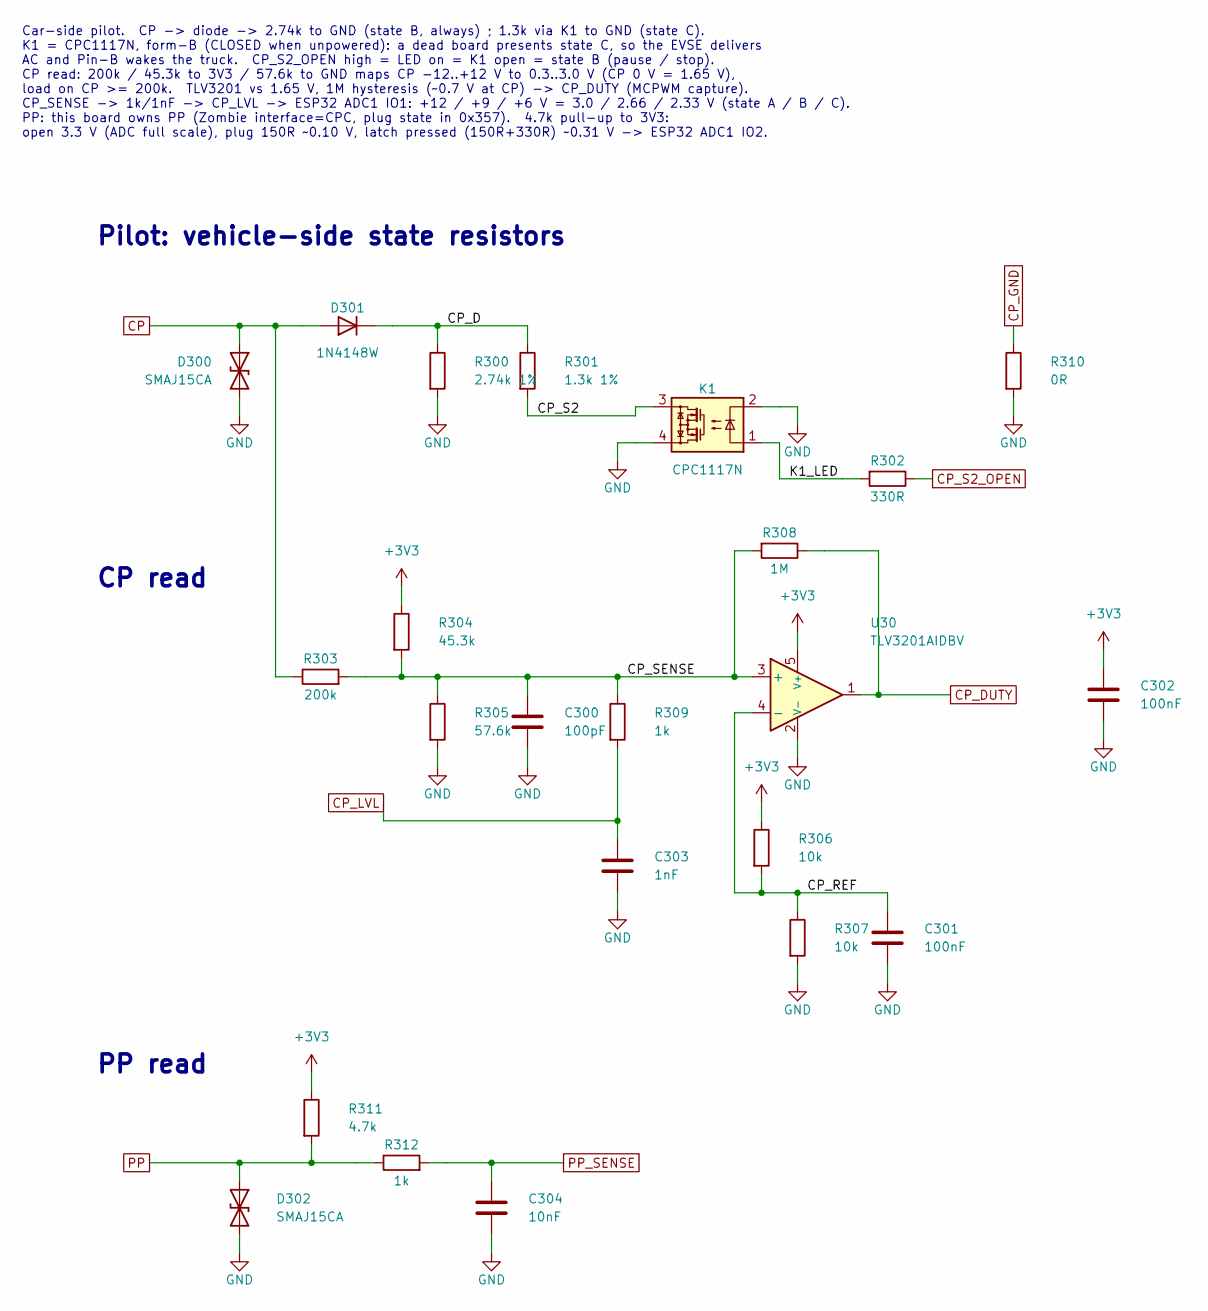
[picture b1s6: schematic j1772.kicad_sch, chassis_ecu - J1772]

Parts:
C300: 100pF; C_0603_1608Metric; MPN CL10C101JB8NNNC; LCSC C14858
C301, C302: 100nF; C_0603_1608Metric; MPN CC0603KRX7R9BB104; LCSC C14663
C303: 1nF; C_0603_1608Metric; MPN CL10B102KB8NNNC; LCSC C1588
C304: 10nF; C_0603_1608Metric; MPN 0603B103K500NT; LCSC C57112
D300, D302: SMAJ15CA; D_SMA; MPN SMAJ15CA; LCSC C19077536
D301: 1N4148W; D_SOD-123; MPN 1N4148W; LCSC C81598
K1: CPC1117N; SOP-4_3.8x4.1mm_P2.54mm; MPN CPC1117NTR; LCSC C150424
R300: 2.74k 1%; R_0805_2012Metric; MPN CR0805-FX-2741ELF; LCSC C204367
R301: 1.3k 1%; R_0805_2012Metric; MPN 0805W8F1301T5E; LCSC C17384
R302: 330R; R_0603_1608Metric; MPN 0603WAF3300T5E; LCSC C23138
R303: 200k; R_0603_1608Metric; MPN 0603WAF2003T5E; LCSC C25811
R304: 45.3k; R_0603_1608Metric; MPN 0603WAF4532T5E; LCSC C23058
R305: 57.6k; R_0603_1608Metric; MPN 0603WAF5762T5E; LCSC C23082
R306, R307: 10k; R_0603_1608Metric; MPN 0603WAF1002T5E; LCSC C25804
R308: 1M; R_0603_1608Metric; MPN 0603WAF1004T5E; LCSC C22935
R309, R312: 1k; R_0603_1608Metric; MPN 0603WAF1001T5E; LCSC C21190
R310: 0R; R_0805_2012Metric; MPN 0805W8F0000T5E; LCSC C17477
R311: 4.7k; R_0603_1608Metric; MPN 0603WAF4701T5E; LCSC C23162
U30: TLV3201AIDBV; SOT-23-5; MPN TLV3201AIDBVR; LCSC C105188

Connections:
+3V3: C302.1, R304.1, R306.1, R311.1, U30.5 (V+); also elsewhere on the board
/J1772/CP_D: D301.1 (K), R300.1, R301.1
/J1772/CP_REF: C301.1, R306.2, R307.1, U30.4 (-)
/J1772/CP_S2: K1.3, R301.2
/J1772/CP_SENSE: C300.1, R303.2, R304.2, R305.1, R308.2, R309.1, U30.3 (+)
/J1772/K1_LED: K1.1, R302.2
CP: D300.1 (A1), D301.2 (A), R303.1; also elsewhere on the board
CP_DUTY: R308.1, U30.1; also elsewhere on the board
CP_GND: R310.1; also elsewhere on the board
CP_LVL: C303.1, R309.2; also elsewhere on the board
CP_S2_OPEN: R302.1; also elsewhere on the board
GND: C300.2, C301.2, C302.2, C303.2, C304.2, D300.2 (A2), D302.2 (A2), K1.2, K1.4, R300.2, R305.2, R307.2, R310.2, U30.2 (V-); also elsewhere on the board
PP: D302.1 (A1), R311.2, R312.1; also elsewhere on the board
PP_SENSE: C304.1, R312.2; also elsewhere on the board

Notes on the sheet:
Pilot: vehicle-side state resistors
Car-side pilot. CP -> diode -> 2.74k to GND (state B, always) ; 1.3k via K1 to GND (state C). K1 = CPC1117N, form-B (CLOSED when unpowered): a dead board presents state C, so the EVSE delivers AC and Pin-B wakes the truck. CP_S2_OPEN high = LED on = K1 open = state B (pause / stop). CP read: 200k /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
PP read
CP read
